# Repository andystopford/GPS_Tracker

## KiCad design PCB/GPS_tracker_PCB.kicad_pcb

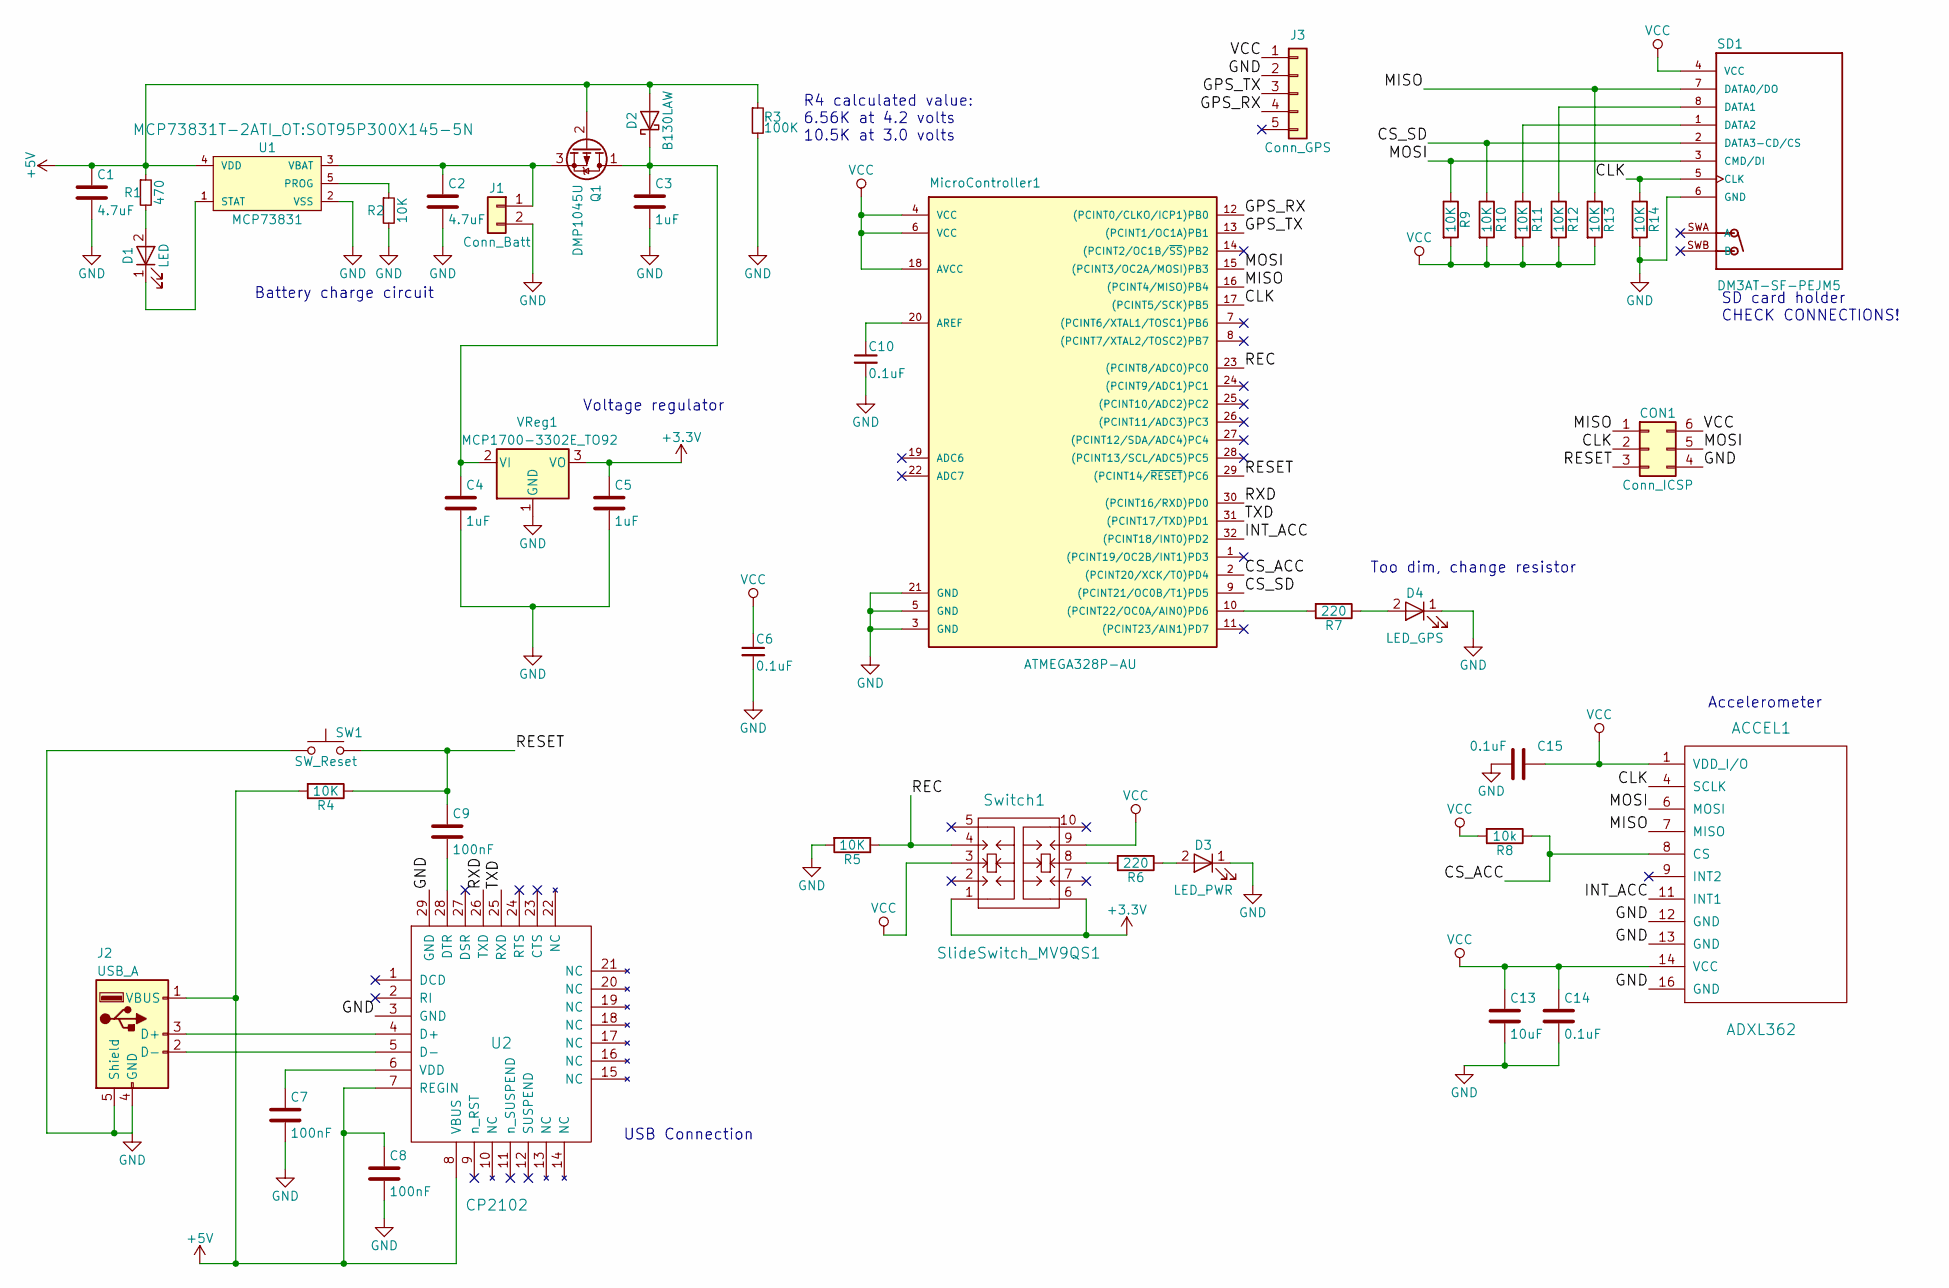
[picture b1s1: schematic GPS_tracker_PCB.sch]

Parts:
ACCEL1: ADXL362; LGA-16_3.25x3.00
C1, C2: 4.7uF; C_1206
C3, C4, C5: 1uF; C_1206
C6, C10, C14, C15: 0.1uF; C_1206
C7, C8, C9: 100nF; C_1206
C13: 10uF; C_1206
CON1: Conn_ICSP; Pin_Header_Straight_2x03_Pitch2.54mm
D1: LED; D_0603
D2: B130LAW; D_SOD-123
D3: LED_PWR; D_0603
D4: LED_GPS; D_0603
J1: Conn_Batt; Pin_Header_Straight_1x02_Pitch2.54mm
J2: USB_A
J3: Conn_GPS; Pin_Header_Straight_1x05_Pitch2.54mm
MicroController1: ATMEGA328P-AU; TQFP-32_7x7mm_Pitch0.8mm
Q1: DMP1045U
R1: 470; R_1206
R2, R4, R5, R9, R10, R11, R12, R13, R14: 10K; R_1206
R3: 100K; R_1206
R6, R7: 220; R_1206
R8: 10k; R_1206
SD1: DM3AT-SF-PEJM5; HRS_DM3AT-SF-PEJM5
SW1: SW_Reset; TactileButton_2Pin
Switch1: SlideSwitch_MV9QS1
U1: MCP73831; SOT95P300X145-5N
U2: CP2102; QFN-28-1EP_5x5mm_Pitch0.5mm
VReg1: MCP1700-3302E_TO92; TO-92_Inline_Wide

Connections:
+3V3: C5.1, Switch1.1, Switch1.6, VReg1.3 (VO)
+5V: C1.1, C8.1, D2.2 (A), J2.1 (VBUS), Q1.2 (G), R1.1, R3.1, R4.2, U1.4 (VDD), U2.7 (REGIN), U2.8 (VBUS)
/CLK: ACCEL1.4 (SCLK), CON1.2, MicroController1.17 ((PCINT5/SCK)PB5), R14.1, SD1.5 (CLK)
/CS_ACC: ACCEL1.8 (CS), MicroController1.2 ((PCINT20/XCK/T0)PD4), R8.1
/CS_SD: MicroController1.9 ((PCINT21/OC0B/T1)PD5), R10.1, SD1.2 (DATA3-CD/CS)
/GPS_RX: J3.4, MicroController1.12 ((PCINT0/CLKO/ICP1)PB0)
/GPS_TX: J3.3, MicroController1.13 ((PCINT1/OC1A)PB1)
/INT_ACC: ACCEL1.11 (INT1), MicroController1.32 ((PCINT18/INT0)PD2)
/MISO: ACCEL1.7 (MISO), CON1.1, MicroController1.16 ((PCINT4/MISO)PB4), R13.1, SD1.7 (DATA0/DO)
/MOSI: ACCEL1.6 (MOSI), CON1.5, MicroController1.15 ((PCINT3/OC2A/MOSI)PB3), R9.1, SD1.3 (CMD/DI)
/REC: MicroController1.23 ((PCINT8/ADC0)PC0), R5.1, Switch1.4
/RESET: C9.1, CON1.3, MicroController1.29 ((PCINT14/~RESET~)PC6), R4.1, SW1.2
/RXD: MicroController1.30 ((PCINT16/RXD)PD0), U2.26 (TXD)
/TXD: MicroController1.31 ((PCINT17/TXD)PD1), U2.25 (RXD)
GND: ACCEL1.12 (GND), ACCEL1.13 (GND), ACCEL1.16 (GND), C1.2, C2.2, C3.2, C4.2, C5.2, C6.2, C7.2, C8.2, C10.2, C13.2, C14.2, C15.2, CON1.4, D3.1 (K), D4.1 (K), J1.2, J2.4 (GND), J2.5 (Shield), J3.2, MicroController1.3 (GND), MicroController1.5 (GND), MicroController1.21 (GND), R2.2, R3.2, R5.2, R14.2, SD1.6 (GND), SW1.1, U1.2 (VSS), U2.3 (GND), U2.29 (GND), VReg1.1 (GND)
unnamed: C2.1, J1.1, Q1.3 (S), U1.3 (VBAT)
unnamed: C3.1, C4.1, D2.1 (K), Q1.1 (D), VReg1.2 (VI)
unnamed: C7.1, U2.6 (VDD)
unnamed: C9.2, U2.28 (DTR)
unnamed: C10.1, MicroController1.20 (AREF)
unnamed: D1.1 (K), U1.1 (STAT)
unnamed: D1.2 (A), R1.2
unnamed: D3.2 (A), R6.1
unnamed: D4.2 (A), R7.1
unnamed: J2.2 (D-), U2.5 (D-)
unnamed: J2.3 (D+), U2.4 (D+)
unnamed: MicroController1.10 ((PCINT22/OC0A/AIN0)PD6), R7.2
unnamed: R2.1, U1.5 (PROG)
unnamed: R6.2, Switch1.8
unnamed: R11.1, SD1.1 (DATA2)
unnamed: R12.1, SD1.8 (DATA1)
VCC: ACCEL1.1 (VDD_I/O), ACCEL1.14 (VCC), C6.1, C13.1, C14.1, C15.1, CON1.6, J3.1, MicroController1.4 (VCC), MicroController1.6 (VCC), MicroController1.18 (AVCC), R8.2, R9.2, R10.2, R11.2, R12.2, R13.2, SD1.4 (VCC), Switch1.3, Switch1.9

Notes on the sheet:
USB Connection
SD card holder CHECK CONNECTIONS!
Battery charge circuit
Voltage regulator
R4 calculated value: 6.56K at 4.2 volts 10.5K at 3.0 volts
Accelerometer
Too dim, change resistor

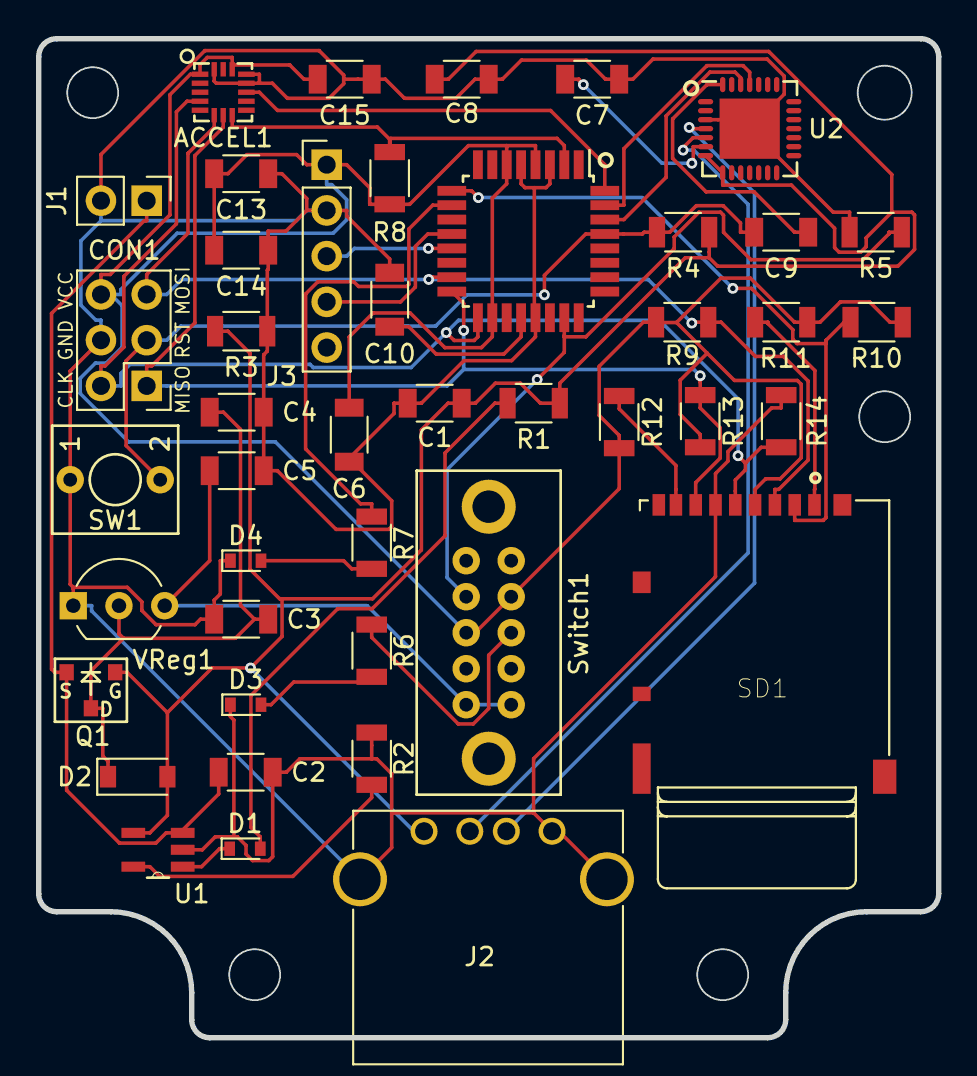
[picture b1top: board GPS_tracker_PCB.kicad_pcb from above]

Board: 2 copper layers, 50.0 x 55.5 mm, 44 parts (0 on the bottom side), 32 nets.

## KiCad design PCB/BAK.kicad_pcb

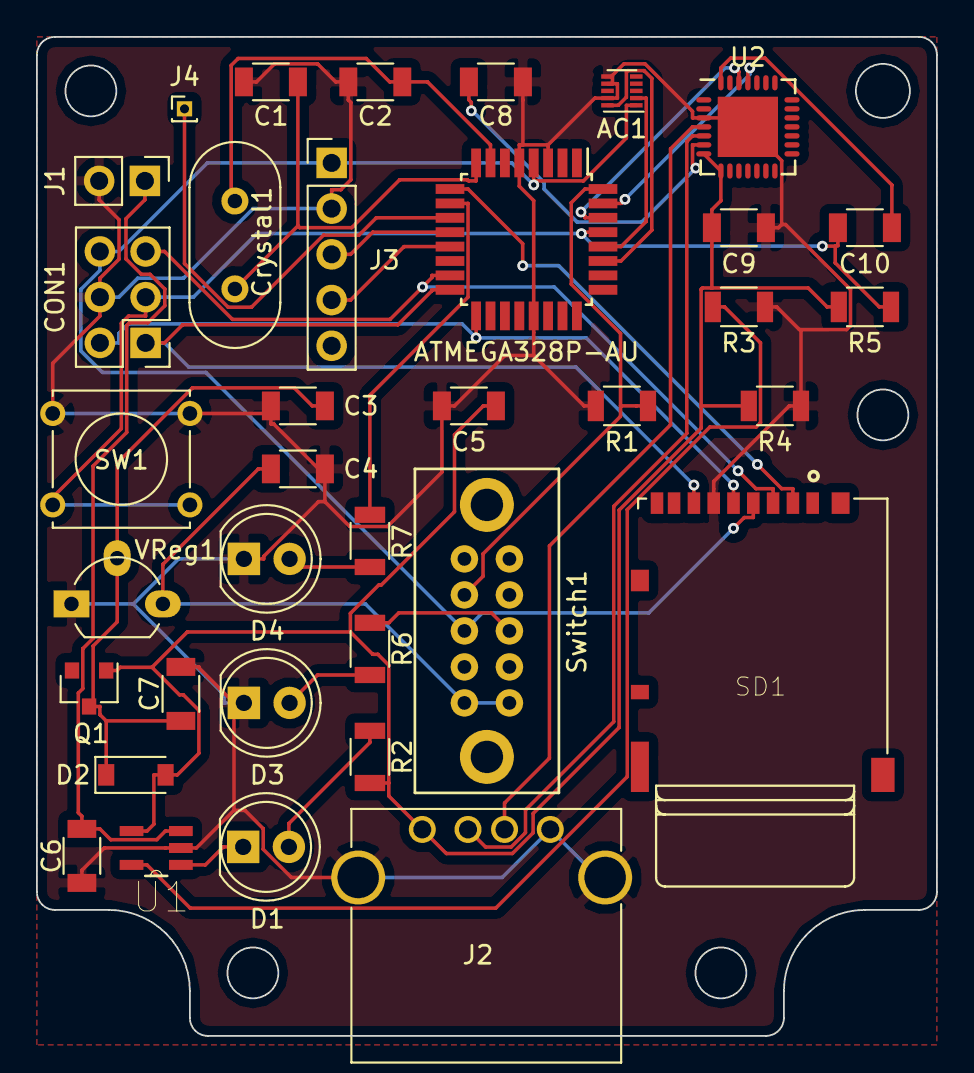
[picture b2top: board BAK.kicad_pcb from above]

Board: 2 copper layers, 50.0 x 55.5 mm, 36 parts (0 on the bottom side), 32 nets.

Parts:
AC1: MMA8652FCR1; DFN-10_2x2mm_Pitch0.4mm
C1, C2, C3, C4: C; C_1206
C5, C6: 4uF; C_1206
C7: 1uF; C_1206
C8, C9, C10: 100nF; C_1206
CON1: Conn_ICSP; Pin_Header_Straight_2x03_Pitch2.54mm
Crystal1: 8MHz; Crystal_HC49-4H_Vertical
D1: LED; LED_D5.0mm
D2: B130LAW; D_SOD-123
D3: LED_PWR; LED_D5.0mm
D4: LED_GPS; LED_D5.0mm
J1: Conn_Batt; Pin_Header_Straight_1x02_Pitch2.54mm
J2: USB_A
J3: Conn_GPS; Pin_Header_Straight_1x05_Pitch2.54mm
J4: Conn_GPS_LED; Pin_Header_Straight_1x01_Pitch1.00mm
MicroController2: ATMEGA328P-AU; TQFP-32_7x7mm_Pitch0.8mm
Q1: DMP1045U; D_SOT-23_ANK
R1, R3, R5: 10K; R_1206
R2: 470; R_1206
R4: 100K; R_1206
R6, R7: 220; R_1206
SD1: DM3AT-SF-PEJM5; HRS_DM3AT-SF-PEJM5
SW1: SW_Reset; SW_Tactile_Straight_KSA0Axx1LFTR
Switch1: SlideSwitch_MV9QS1
U1: MCP73831; SOT95P300X145-5N
U2: CP2102; QFN-28-1EP_5x5mm_Pitch0.5mm
VReg1: MCP1700-3302E_TO92; TO-92_Molded_Wide_Oval

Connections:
+3V3: C4.1, Switch1.1, Switch1.6, VReg1.3
+5V: C5.1, C9.1, D2.2, J2.1, Q1.2, R2.1, R4.1, R5.2, U1.4, U2.7, U2.8
/CLK: CON1.2, MicroController2.17, SD1.5
/CS_SD: MicroController2.9, SD1.2
/GPS_RX: J3.4, MicroController2.13
/GPS_TX: J3.3, MicroController2.12
/MISO: CON1.1, MicroController2.16, SD1.7
/MOSI: CON1.5, MicroController2.15, SD1.3
/REC: MicroController2.32, R1.1, Switch1.4
/RESET: C10.1, CON1.3, MicroController2.29, R5.1, SW1.2
/RXD: MicroController2.30, U2.26
/SCL: AC1.2, MicroController2.28
/SDA: AC1.10, MicroController2.27
/TXD: MicroController2.31, U2.25
/VCC: AC1.1, CON1.6, J3.1, MicroController2.4, SD1.4, Switch1.3
GND: AC1.6, AC1.7, AC1.9, C1.2, C2.2, C3.2, C4.2, C5.2, C6.2, C7.2, C8.2, C9.2, CON1.4, D3.1, D4.1, J1.2, J2.4, J2.5, J3.2, MicroController2.3, MicroController2.5, MicroController2.21, R1.2, R3.2, R4.2, SD1.6, SW1.1, U1.2, U2.3, U2.29, VReg1.1
unnamed: C1.1, Crystal1.1, MicroController2.8
unnamed: C2.1, Crystal1.2, MicroController2.7
unnamed: C3.1, C7.1, D2.1, Q1.1, VReg1.2
unnamed: C6.1, J1.1, U1.3
unnamed: C8.1, U2.6
unnamed: C10.2, U2.28
unnamed: D1.1, U1.1
unnamed: D1.2, R2.2
unnamed: D3.2, R6.1
unnamed: D4.2, R7.1
unnamed: J2.2, U2.5
unnamed: J2.3, U2.4
unnamed: J4.1, MicroController2.11
unnamed: MicroController2.10, R7.2
unnamed: R3.1, U1.5
unnamed: R6.2, Switch1.8

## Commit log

2018-02-08 Initial commit.
2018-06-07 Current working version, most junk cleared out.
2018-06-07 Current version
